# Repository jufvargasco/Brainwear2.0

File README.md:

# Brainwear board

The Brainwear board is an open-source EEG sensing driver module is designed with the state-of-the-art analog front-end that is pin-compatible with the popular Feather ecosystem in the wearable and DIY community.

## Hardware description

The Brainwear board was made using the Texas Instruments Analog Front-End ADS1299. This SOC incorporates low-power technology and integrates instrumentation amplifiers, operational amplifiers, and analog to digital converters into a single IC. Hence, it is ideal for biopotential measurements such as EEG, ECG, and EOG as it provides eight different channels with a 24-bit resolution and a sampling rate of 250 Hz. Additionally, it includes attractive characteristics such as test signals for impedance measurement and SPI compatible interface.

The Brainwear board is a mixed-signal system that combines both analog and digital components. Since both components are present in a single circuit, the analog circuit is susceptible to crosstalk noise generated by the digital circuit via stray capacitances. As a result, the small EEG signals acquired by the AFE can easily be distorted and provide erroneous measurements. The crosstalk noise was avoided by using a fully isolated circuit design technique. That is, separated ground planes for digital and analog signals and isolated analog and digital interfaces at each side of the board. Moreover, we used Low-Dropout linear regulators (MCP1754T-3302, TPS72325, TLV70025) and a voltage inverter (TCM828) to provide the analog bipolar supply of +- 2.5V and the digital supply of + 3.3V. The control signals of these devices were also isolated from the ground planes to avoid the switching noise generated by the voltage inverter.  

The feather board powers the Brainwear board. Then, a voltage detection IC (BD5330G) is used to disconnect the circuit once the supply voltage is lower than 3V to protect the battery. The ADS1299 is connected in a referential montage. Thus, eight different channels can be measured in reference to the input SRB1. The AFE also offers the possibility of measuring the bias in the signals using the Bias input included in the PCB. Electrostatic discharge chips were included to protect the channels of the board as well as the main analog and digital signals in the circuit.
Additionally, an LED (GPIO4) was added to provide an easy way to test the SPI communication between the main board and the Brainwear module. Hardware filters were included following the references provided by Texas Instruments and OpenBCI. Finally, an SD module was integrated into the board in order to record EEG data when required. It is essential to mention that the ADS1299 and the SD card do not share the same SPI bus. Hence, the ADS1299 is connected to the predetermined SPI pins of the feather board, while the SD card requires configuring the board's upper pins to act as an SPI bus.

The KiCAD files with the PCB of the Brainwear board are in the folder Design Files

## Firmware description
The firmware shows an application example in the file Brainwear_test.ino. The program contains two different types of classes: the first one is used for instantiating the Brainwear board while the second allows to add the Mechanomyography sensors whose signals are acquired with the TI-ADS1015. The first class packages all the functionalities available in the Brainwear hardware, i.e. testing signals, register, channel, and sample rate configuration, among others. This code is based on the OpenBCI firmware for the Cyton board. On the other hand, the second class allows to instantiate one board of the ADS1015 according to the required sample rate and gain. It also includes functionalities to send data to the main board according to the type of transmissions.

The system receives commands via the serial port that allow to configure the way the board behaves. A description of the commands is given below. Further information about the commands can be found in the file Brainwear_definitions.h

### Commands
#### Multichar commands
1. Channel settings

This command requires multiple characters to be recognized. It consists of seven different settings group together corresponding to the channel to modify, power-down, gain, type of input, bias generation, connection to SRB2, connection to SRB1, respectively. The code starts with lower x and end with capital X.

Example:
<p align="center">
    x1060001X
</p>

This code sets the channel (1) to power-down on (0), gain of 24 (6), normal input (0), remove bias (0), disconnected of SRB2 (0) and connected to SRB1 (1)

2. Leadoff settings

This command requires multiple characters to be recognized. It consists of 3 different settings group together corresponding to the channel to modify and the activation of the Lead off for the channel P and the channel N of the specified channel, respectively. The code starts with lower z and end with capital Z.

Example:
<p align="center">
    z111Z
</p>

This code sets the Leadoff detection for the channel (1) to (1 / activated) for the P channel and to (1 / activated) for the N channel.

3. Sample rate settings
 
This command requires multiple characters to be recognized. It consists of the character ~ followed by the desired sample rate for the board. The options are shown below.

| Command | Sample Rate |
|---------|-------------|
| 0       | 16 KHz      |
| 1       | 8 KHz       |
| 2       | 4 KHz       |
| 3       | 2 KHz       |
| 4       | 1 KHz       |
| 5       | 500 Hz      |
| 6       | 250 Hz      |

Example:
<p align="center">
    ~6
</p>

This code sets the sample rate of the board to 250 Hz.

#### Single commands

The single commands to manipulate the Brainwear board as described in the following table.

| Command | Description |
|---------|-------------|
| 1       | Deactivate channel 1      |
| 2       | Deactivate channel 2      |
| 3       | Deactivate channel 3      |
| 4       | Deactivate channel 4      |
| 5       | Deactivate channel 5      |
| 6       | Deactivate channel 6      |
| 7       | Deactivate channel 7      |
| 8       | Deactivate channel 8      |
| Q       | Activate channel 1        |
| W       | Activate channel 2        |
| E       | Activate channel 3        |
| R       | Activate channel 4        |
| T       | Activate channel 5        |
| Y       | Activate channel 6        |
| U       | Activate channel 7        |
| I       | Activate channel 8        |
| p       | Connect channels to DC Test signal      | 
| 0       | Connect channels to GND Test signal     | 
| =       | Connect channels to fast 1X Test signal | 
| -       | Connect channels to slow 1X signal      | 
| ]       | Connect channels to fast 2X Test signal | 
| \[      | Connect channels to slow 2X Test signal | 
| n       | Connect channels to normal input        | 
| d       | Set all channels to default settings      |
| D       | Report the default settings        |
| C       | Report number of channels in board      |
| t       | Activate serial stream of data       |
| y       | Deactivate serial stream of data       |
| b       | Start streaming data       |
| s       | Stop streaming data         |
| ?       | Show the register settings of the ADS1299 board       |
| v       | Soft reset of the board        |
| V       | Get firmware version        |
| l       | Turn on LED on the Brainwear board      |
| k       | Turn off LED on the Brainwear board      |
| a       | Activate recording with the SD card      |
| r       | Reset file counter for the SD files      |
| j       | Close SD file      |
| A       | Record 1 minute of activity in the SD      |
| S       | Record 5 minutes of activity in the SD       |
| F       | Record 15 minutes of activity in the SD      |
| G       | Record 30 minutes of activity in the SD         |
| H       | Record 1 hour of activity in the SD        |
| J       | Record 2 hours of activity in the SD        |
| K       | Record 4 hours of activity in the SD         |
| <       | Set transmission to RAW mode (compatible with OpenBCI)        |
| >       | Set transmission to ASCII mode (compatible with Arduino plotter)        |
| M       | Activate multimode (EEG + MMG)       |
| N       | Deactivate multimode  (Only EEG is active)       |

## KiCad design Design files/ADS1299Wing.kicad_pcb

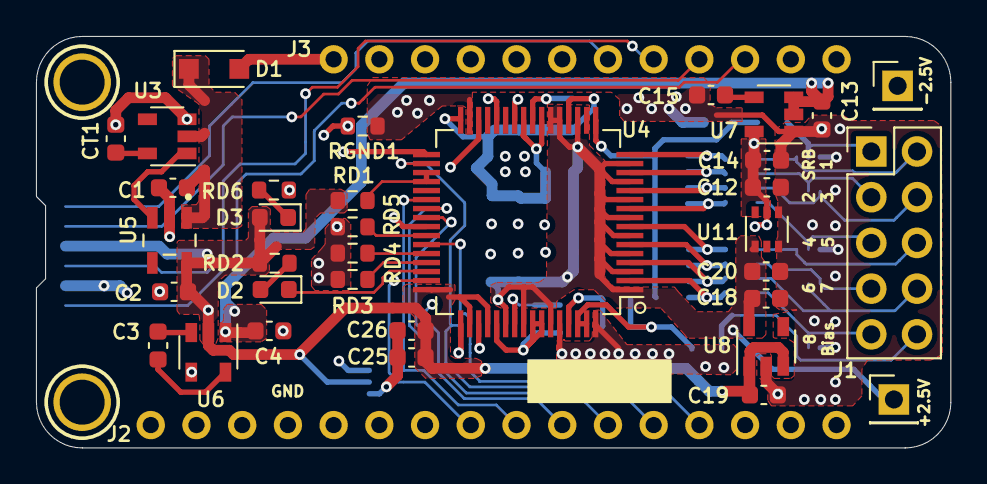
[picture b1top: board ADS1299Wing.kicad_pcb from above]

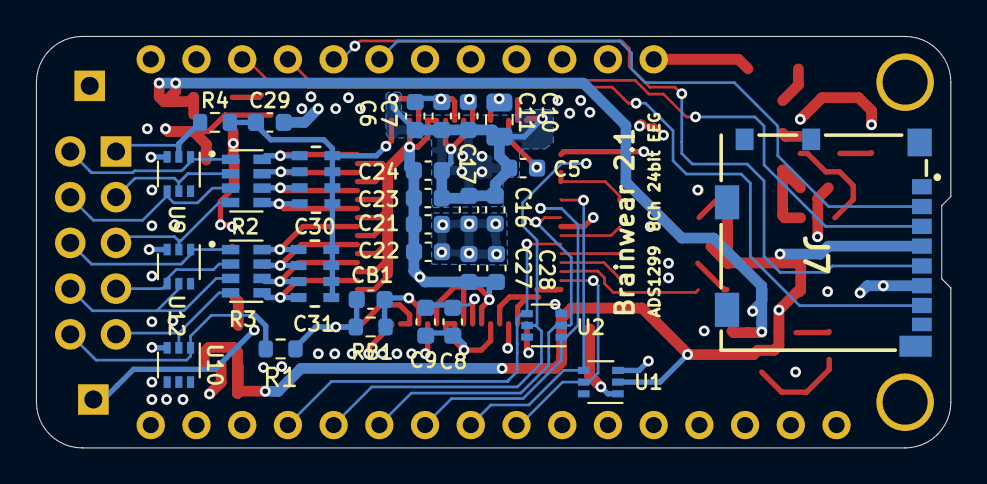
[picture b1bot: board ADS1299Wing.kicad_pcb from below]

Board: 4 copper layers, 50.8 x 22.9 mm, 68 parts (30 on the bottom side), 56 nets.

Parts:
+2.5V: Conn_01x01; PinHeader_1x01_P2.54mm_Vertical
-2.5V: Conn_01x01; PinHeader_1x01_P2.54mm_Vertical
C1, C2, C13, C14, C19, C20: 2.2uF; C_0603_1608Metric
C3, C4, C6, C12, C18: 10uF; C_0603_1608Metric
C5, C9, C11, C16, C21, C23, C25, C27: 1uF; C_0603_1608Metric
C7, C17, C22, C24, C26, C28: 0.1uF; C_0603_1608Metric
C8: 100nF; C_0603_1608Metric
C10: 100uF; C_0805_2012Metric
C15: 0.01uF; C_0603_1608Metric
C29: 1nF; C_0603_1608Metric
C30, C31: CA064C102K5RACTU
CB1: 1nF; C_0603_1608Metric
CT1: 1nF; C_0603_1608Metric
D1: MBR120; D_SOD-123F
D2, D3: LED_Small; LED_0603_1608Metric
J1: Conn_02x05_Top_Bottom; PinHeader_2x05_P2.54mm_Vertical
J2: Conn_01x16; 1X16_ROUND_MIN
J3: Conn_01x12; 1X12_ROUND_MIN
J7: 104031-0811; 1040310811
MH1, MH2: M_HOLE2.5; MH2.5
R1, R4: 2.2K; R_0603_1608Metric
R2, R3: CAY16-2201F4LF; RESCAF80P320X160X60-8N
RB1: 1MOhm; R_0603_1608Metric
RD1: 1M; R_0603_1608Metric
RD2: 470; R_0603_1608Metric
RD3, RD4, RD5: 10K; R_0603_1608Metric
RD6: 1k; R_0603_1608Metric
RGND1: R_Small; R_0603_1608Metric
U1, U2, U9, U10, U11, U12: TPD4E1B06DCK; SOT-363_SC-70-6
U3: BD5330G; SOT-23-5
U4: ADS1299; TQFP-64_10x10mm_P0.5mm
U5: MCP1754T-3302E_OT; SOT95P280X145-5N
U6: TCM828; SOT-23-5
U7: TPS72325; SOT-23-5
U8: TLV70025; SOT-23-5

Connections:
+2V5: +2.5V.1, C18.1, C20.1, C21.1, C22.1, C23.1, C24.1, C27.1, C28.1, U4.1, U4.3, U4.5, U4.7, U4.9, U4.11, U4.13, U4.15, U4.19, U4.21, U4.22, U4.54, U4.56, U4.59, U8.5, U11.1
+3V3: C2.1, C19.1, C25.1, C26.1, D3.2, J7.4, RD1.2, RD2.2, U1.2, U4.48, U4.50, U4.52, U5.5, U6.2, U8.1, U8.3
+BATT: C1.1, D1.1, U3.2, U5.1
+EXT_BATT: D1.2, J3.1
-2V5: -2.5V.1, C5.2, C6.2, C7.2, C8.2, C9.2, C10.2, C11.2, C12.1, C14.1, C16.1, C17.1, C23.2, C24.2, U4.20, U4.23, U4.25, U4.32, U4.53, U4.57, U4.58, U7.5, U11.5
-3V3: C4.1, C13.1, U6.1, U7.2, U7.3
/DIN: J2.5, U2.5, U4.34
/DOUT: J2.4, U2.4, U4.43
/SCLK: J2.6, U2.2, U4.40
/START: J2.8, U1.4, U4.38
/V_EN: U3.1, U5.3
/~CS: J2.7, U2.1, U4.39
/~DRDY: J2.9, U1.5, U4.47
/~PWDN\RST: RD1.1, U4.35, U4.36
Bias: CB1.1, R1.2, RB1.2, U4.62, U4.63
Bias_e: J1.10, R1.1, U10.1
GND: C1.2, C2.2, C4.2, C25.2, C26.2, CT1.1, J2.13, J7.6, RD3.2, RD4.2, RD5.2, RD6.2, RGND1.2, U1.1, U1.3, U2.3, U3.3, U4.33, U4.41, U4.49, U4.51, U5.2, U6.4
GNDA: C12.2, C13.2, C14.2, C15.2, C16.2, C17.2, C18.2, C19.2, C20.2, C21.2, C22.2, C27.2, C28.2, C29.2, RGND1.1, U4.31, U4.60, U4.64, U7.1, U8.2, U9.3, U10.3, U11.3, U11.4, U12.3
IN1P: C30.1, R2.8, U4.16
IN1P_e: J1.2, R2.1, U9.1
IN2P: C30.2, R2.7, U4.14
IN2P_e: J1.3, R2.2, U9.5
IN3P: C30.3, R2.6, U4.12
IN3P_e: J1.4, R2.3, U9.4
IN4P: C30.4, R2.5, U4.10
IN4P_e: J1.5, R2.4, U12.2
IN5P: C31.1, R3.8, U4.8
IN5P_e: J1.6, R3.1, U12.1
IN6P: C31.2, R3.7, U4.6
IN6P_e: J1.7, R3.2, U12.4
IN7P: C31.3, R3.6, U4.4
IN7P_e: J1.8, R3.3, U12.5
IN8P: C31.4, R3.5, U4.2
IN8P_e: J1.9, R3.4, U10.2
MISO: J3.10, J7.7
MOSI: J3.9, J7.3
unnamed: C3.1, U6.5
unnamed: C3.2, U6.3
unnamed: C5.1, U4.30
unnamed: C6.1, C7.1, U4.24
unnamed: C8.1, C9.1, U4.55
unnamed: C10.1, U4.28
unnamed: C11.1, U4.26
unnamed: C15.1, U7.4
unnamed: CB1.2, RB1.1, U4.61
unnamed: CT1.2, U3.5
unnamed: D2.1, U4.46
unnamed: D2.2, RD2.1
unnamed: D3.1, RD6.1
unnamed: RD3.1, U4.45
unnamed: RD4.1, U4.44
unnamed: RD5.1, U4.42
SD_CS: J3.7, J7.2
SD_SCLK: J3.8, J7.5
SRB1: C29.1, C30.5, C30.6, C30.7, C30.8, C31.5, C31.6, C31.7, C31.8, R4.2, U4.17
SRB1_e: J1.1, R4.1, U9.2

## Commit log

2021-05-26 Addition of Hardware files
2021-06-16 Addition of images
2021-06-16 Addition of Brainwear firmware
2021-06-16 Modification of Gerber files
2022-04-07 Addition of datasets

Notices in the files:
parts and their libraries:
Copyright 2016 Accelerated Designs. All rights reserved.
